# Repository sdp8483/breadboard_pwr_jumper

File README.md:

# Breadboard Power Jumper

The *Breadboard Power Jumper* connects the edge rails (bus strips) of a standard solderless breadboard together while also providing clip points for power leads. This design was heavily influenced by a design from [IMSAI Guy](https://www.youtube.com/watch?v=gdtfjXa2s7k&t) with slight modifications to the pcb shape and the addition of manufactured test points.

## BOM
| Item | Description | Qty | Notes |
| ---- | ----------- | --- | ----- |
| PCB  | PCB | 1 | manufactured by PCB prototype service |
| Test Point | [Keystone Electronics 5280](https://www.digikey.com/en/products/detail/keystone-electronics/5280/12751667) | 1 | Red |
| Test Point | [Keystone Electronics 5281](https://www.digikey.com/en/products/detail/keystone-electronics/5281/12751648) | 1 | Black |
| Male Header | [Adam Tech PH2-06-UA](https://www.digikey.com/en/products/detail/adam-tech/PH2-06-UA/9830396) | 2 | any similar 6 position 2 row male header will work|
| 0.1uF 0805 Capacitor | | 2 | Optional or maybe [10uF](https://blog.poly.nomial.co.uk/2025-01-25-proper-decoupling-practices-and-why-you-should-leave-100nf-behind.html) |

## Directory Outline
- [`~/mechanical/`](mechanical): FreeCAD file generated using KiCadStepUp plugin
- [`~/pcb/`](pcb): KiCAD design files
    - [`/pcb/gerber`](pcb/gerber/): files for upload to PCB manufacturing service
    - [`/pcb/pcb_render`](pcb/pcb_render/): PNG image of PCB exported from KiCAD 3D viewer
    - [`/pcb/schematic_pdf`](pcb/schematic_pdf/): schematic exported from KiCAD as a PDF

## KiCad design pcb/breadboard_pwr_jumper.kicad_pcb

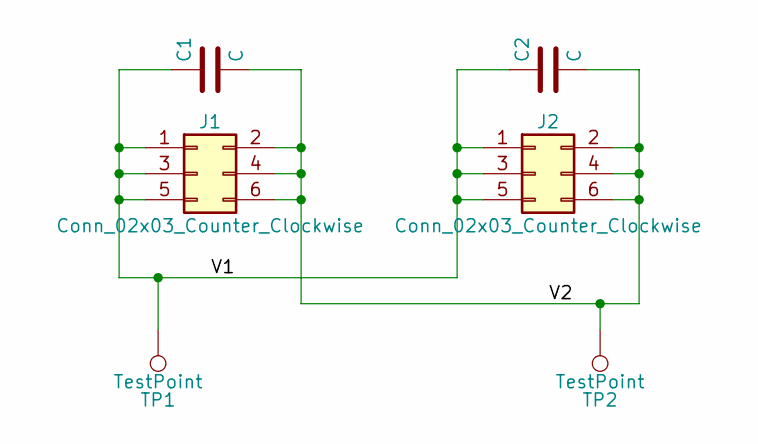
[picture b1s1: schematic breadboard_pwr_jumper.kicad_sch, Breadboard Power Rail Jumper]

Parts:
C1, C2: C; C_0805_2012Metric_Pad1.18x1.45mm_HandSolder
J1, J2: Conn_02x03_Counter_Clockwise; PinHeader_2x03_P2.54mm_Vertical
TP1, TP2: TestPoint; TestPoint_Loop_D2.60mm_Drill1.6mm_Beaded

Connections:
/V1: C1.1, C2.1, J1.1, J1.3, J1.5, J2.1, J2.3, J2.5, TP1.1
/V2: C1.2, C2.2, J1.2, J1.4, J1.6, J2.2, J2.4, J2.6, TP2.1

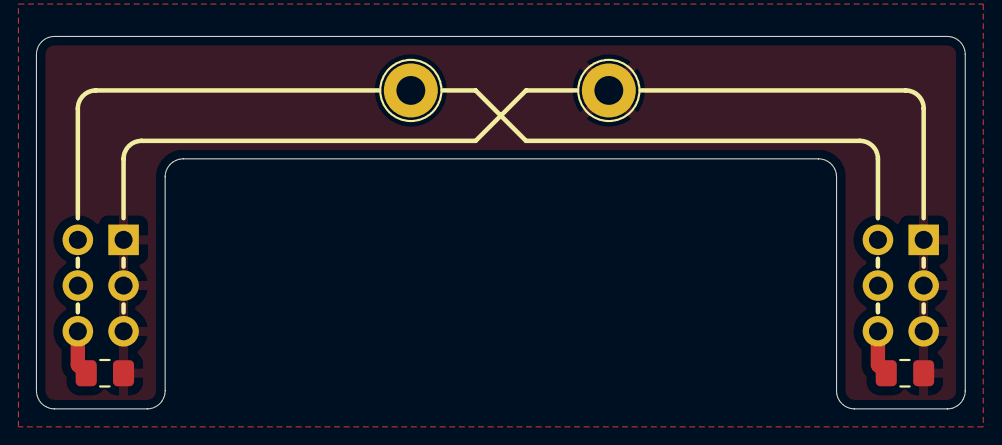
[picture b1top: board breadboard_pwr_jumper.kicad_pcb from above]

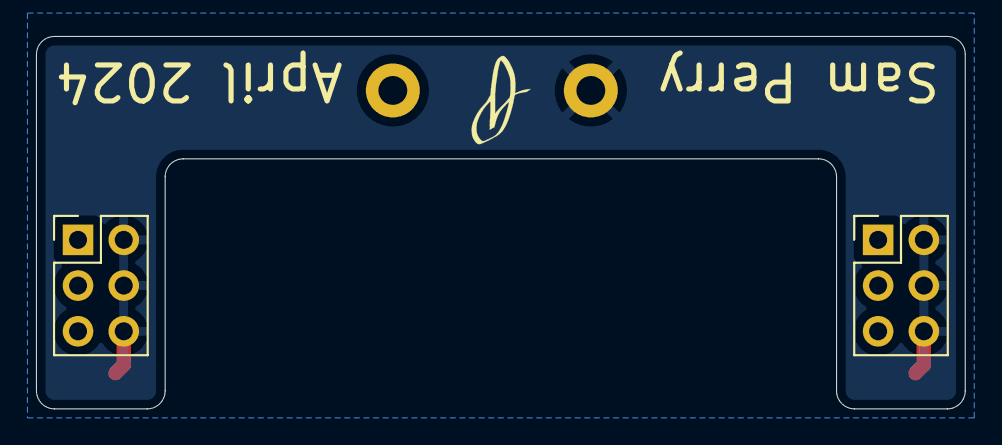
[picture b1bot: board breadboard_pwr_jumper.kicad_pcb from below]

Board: 2 copper layers, 51.6 x 20.7 mm, 6 parts (2 on the bottom side), 2 nets.

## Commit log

2024-04-21 init commit
2024-04-21 create pcb
2024-04-21 export gerbers
2025-03-18 generate exports
2025-03-18 crop image
2025-03-18 update with project specific language
2025-03-18 youtube link without timestamp
2025-03-18 add more photos
2025-03-18 add in use photo
